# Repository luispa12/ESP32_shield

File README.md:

This proyect consist on my first IOT project designed and assambled in Guatemala <3>.
For this project we must do all the process for the design, PCB manufacture (JLCPCB) , troubleshooting and full functionality of the project, in order to meet the requirements to approve the course.
This project must have the process of the hardware design, software, and my own APP.

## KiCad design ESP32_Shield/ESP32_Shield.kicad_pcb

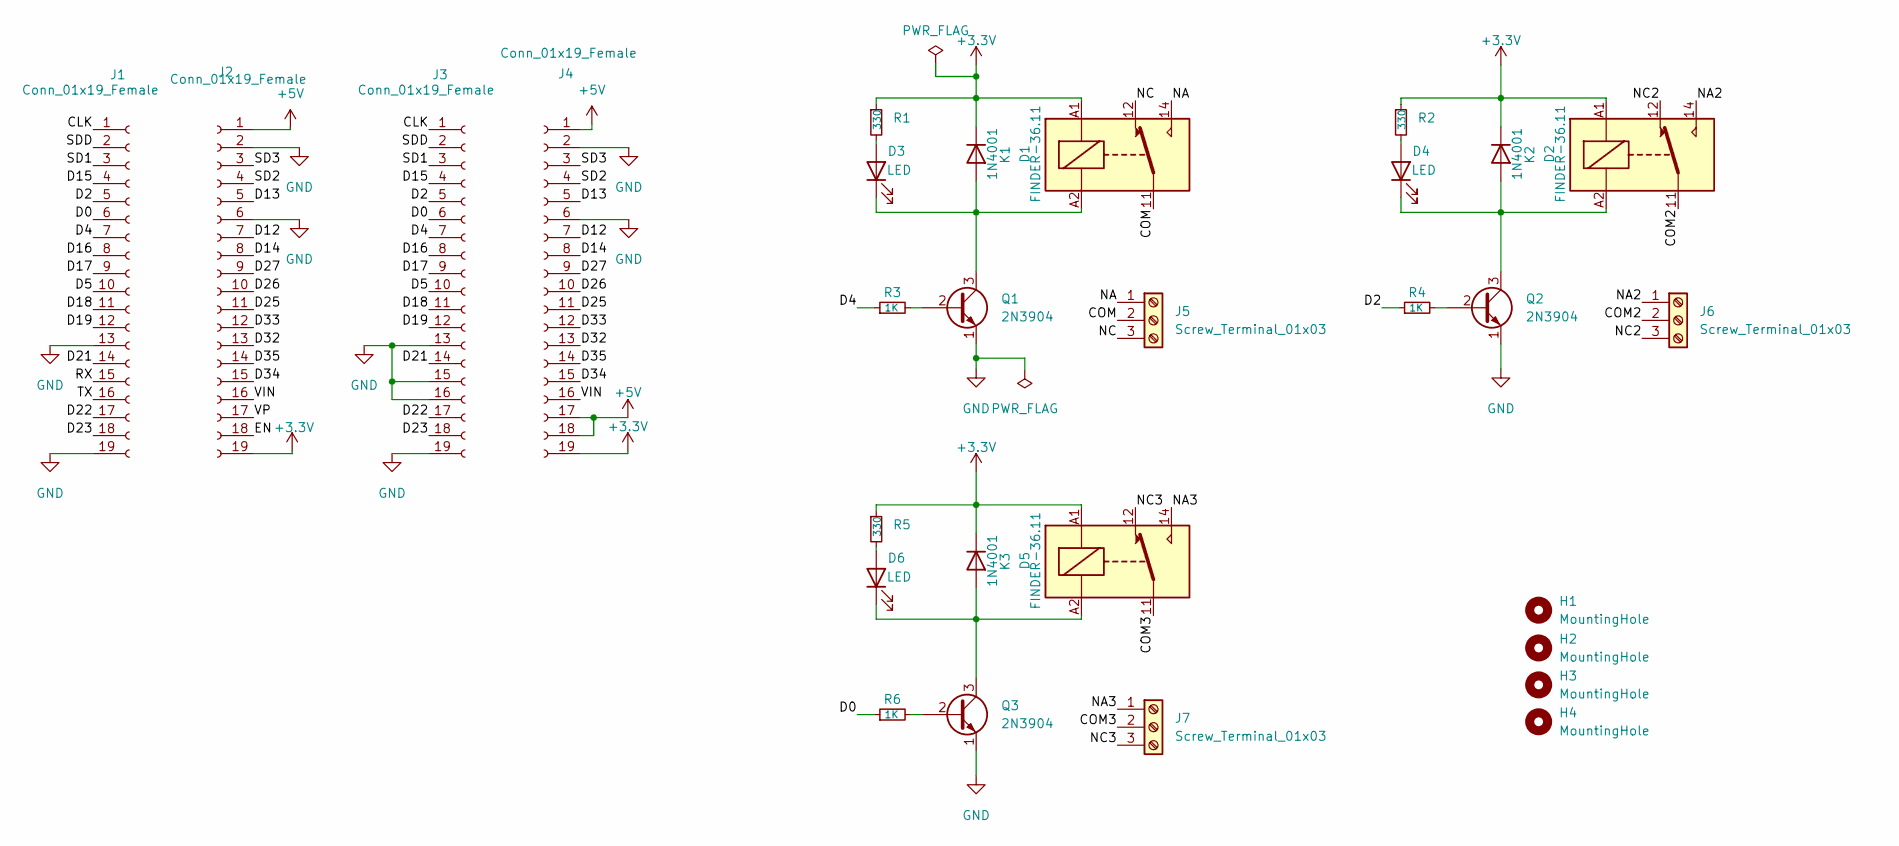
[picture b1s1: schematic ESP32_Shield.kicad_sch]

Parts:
D1, D2, D5: 1N4001; D_0805_2012Metric
D3, D4, D6: LED; LED_0805_2012Metric
H1, H2, H3, H4: MountingHole; MountingHole_2.2mm_M2
J1, J2, J3, J4: Conn_01x19_Female; PinHeader_1x19_P2.54mm_Vertical
J5, J6, J7: Screw_Terminal_01x03; TerminalBlock_Altech_AK300-3_P5.00mm
K1, K2, K3: FINDER-36.11; Relay_SPDT_Finder_36.11
Q1, Q2, Q3: 2N3904; SOT-23
R1, R2, R5: 330; R_0805_2012Metric
R3, R4, R6: 1K; R_0805_2012Metric

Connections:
+3.3V: D1.1 (K), D2.1 (K), D5.1 (K), J2.19, J4.19, K1.A1, K2.A1, K3.A1, R1.1, R2.1, R5.1
+5V: J2.1, J4.1, J4.17, J4.18
/CLK: J1.1, J3.1
/COM: J5.2, K1.11
/COM2: J6.2, K2.11
/COM3: J7.2, K3.11
/D0: J1.6, J3.6, R6.1
/D2: J1.5, J3.5, R4.1
/D4: J1.7, J3.7, R3.1
/D5: J1.10, J3.10
/D12: J2.7, J4.7
/D13: J2.5, J4.5
/D14: J2.8, J4.8
/D15: J1.4, J3.4
/D16: J1.8, J3.8
/D17: J1.9, J3.9
/D18: J1.11, J3.11
/D19: J1.12, J3.12
/D21: J1.14, J3.14
/D22: J1.17, J3.17
/D23: J1.18, J3.18
/D25: J2.11, J4.11
/D26: J2.10, J4.10
/D27: J2.9, J4.9
/D32: J2.13, J4.13
/D33: J2.12, J4.12
/D34: J2.15, J4.15
/D35: J2.14, J4.14
/EN: J2.18
/NA: J5.1, K1.14
/NA2: J6.1, K2.14
/NA3: J7.1, K3.14
/NC: J5.3, K1.12
/NC2: J6.3, K2.12
/NC3: J7.3, K3.12
/RX: J1.15
/SD1: J1.3, J3.3
/SD2: J2.4, J4.4
/SD3: J2.3, J4.3
/SDD: J1.2, J3.2
/TX: J1.16
/VIN: J2.16, J4.16
/VP: J2.17
GND: J1.13, J1.19, J2.2, J2.6, J3.13, J3.15, J3.16, J3.19, J4.2, J4.6, Q1.1 (E), Q2.1 (E), Q3.1 (E)
unnamed: D1.2 (A), D3.1 (K), K1.A2, Q1.3 (C)
unnamed: D2.2 (A), D4.1 (K), K2.A2, Q2.3 (C)
unnamed: D3.2 (A), R1.2
unnamed: D4.2 (A), R2.2
unnamed: D5.2 (A), D6.1 (K), K3.A2, Q3.3 (C)
unnamed: D6.2 (A), R5.2
unnamed: Q1.2 (B), R3.2
unnamed: Q2.2 (B), R4.2
unnamed: Q3.2 (B), R6.2

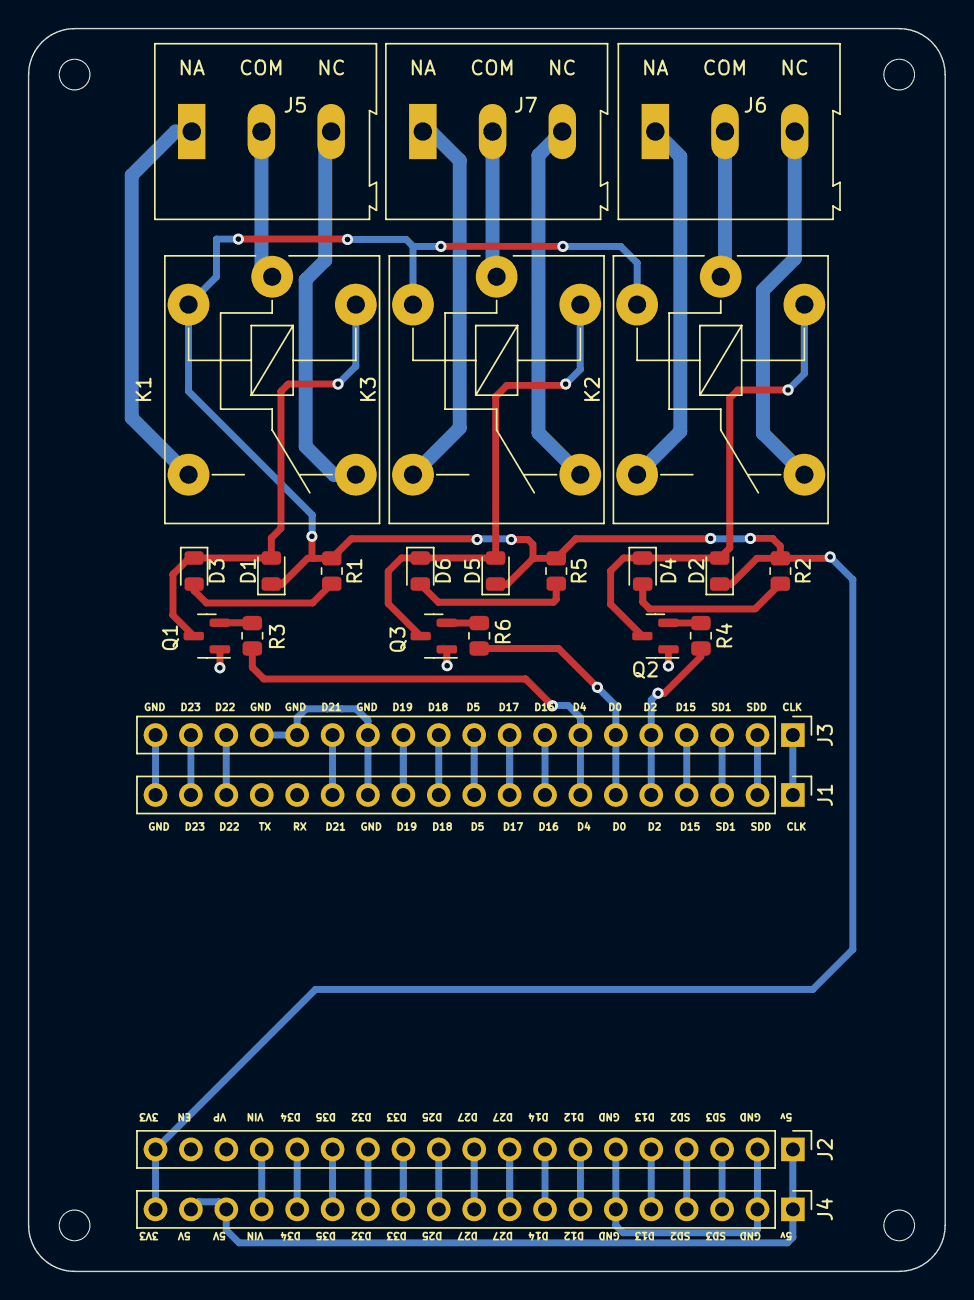
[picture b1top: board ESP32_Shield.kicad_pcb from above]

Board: 2 copper layers, 65.8 x 89.1 mm, 29 parts (0 on the bottom side), 49 nets.

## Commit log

2023-05-22 readme: partial readme writen, must verify the spelling and check if something else will be added, like photos of the board, etc.
2023-05-31 SCH: created te connections for the headers and to embed the ESP32 module, and also did the wiring of the relay.
2023-06-05 PCB: layout completeded
2023-06-05 PCB: added the last power plane
2023-06-05 fabrication files created
